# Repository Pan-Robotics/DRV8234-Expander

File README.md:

# DRV8234-Expander
Breakout PCB for The DRV8234 DC Motor Driver

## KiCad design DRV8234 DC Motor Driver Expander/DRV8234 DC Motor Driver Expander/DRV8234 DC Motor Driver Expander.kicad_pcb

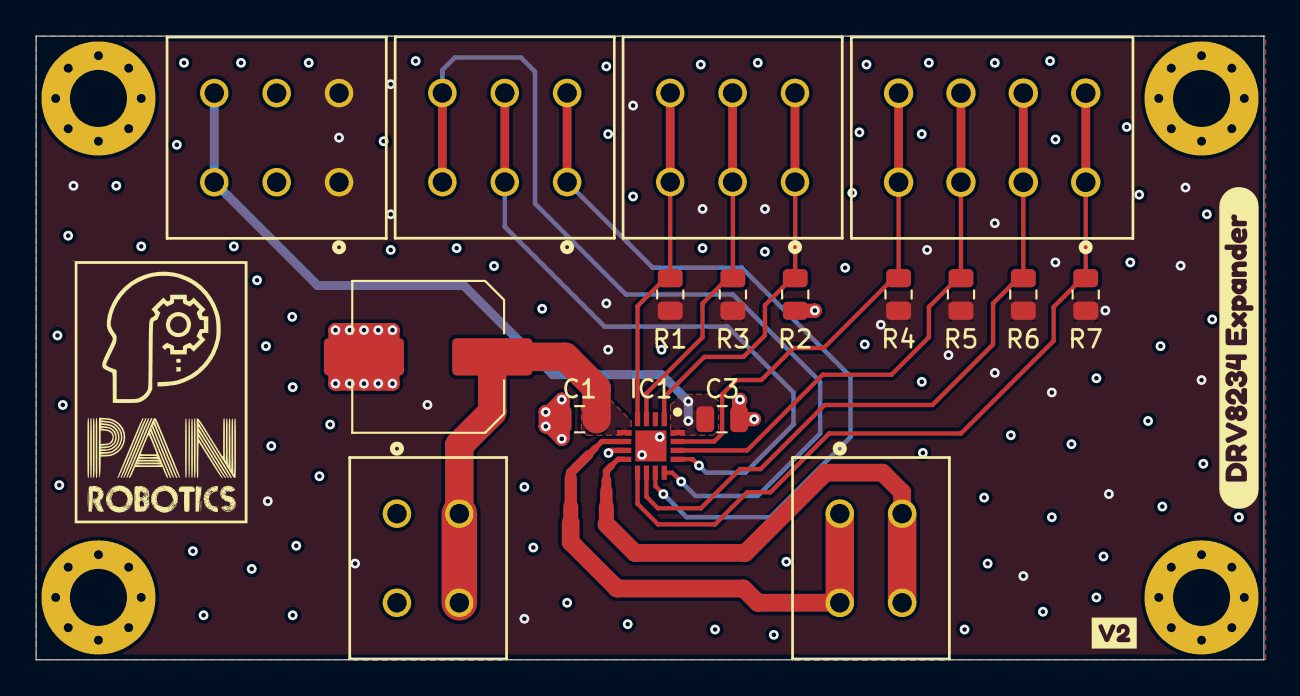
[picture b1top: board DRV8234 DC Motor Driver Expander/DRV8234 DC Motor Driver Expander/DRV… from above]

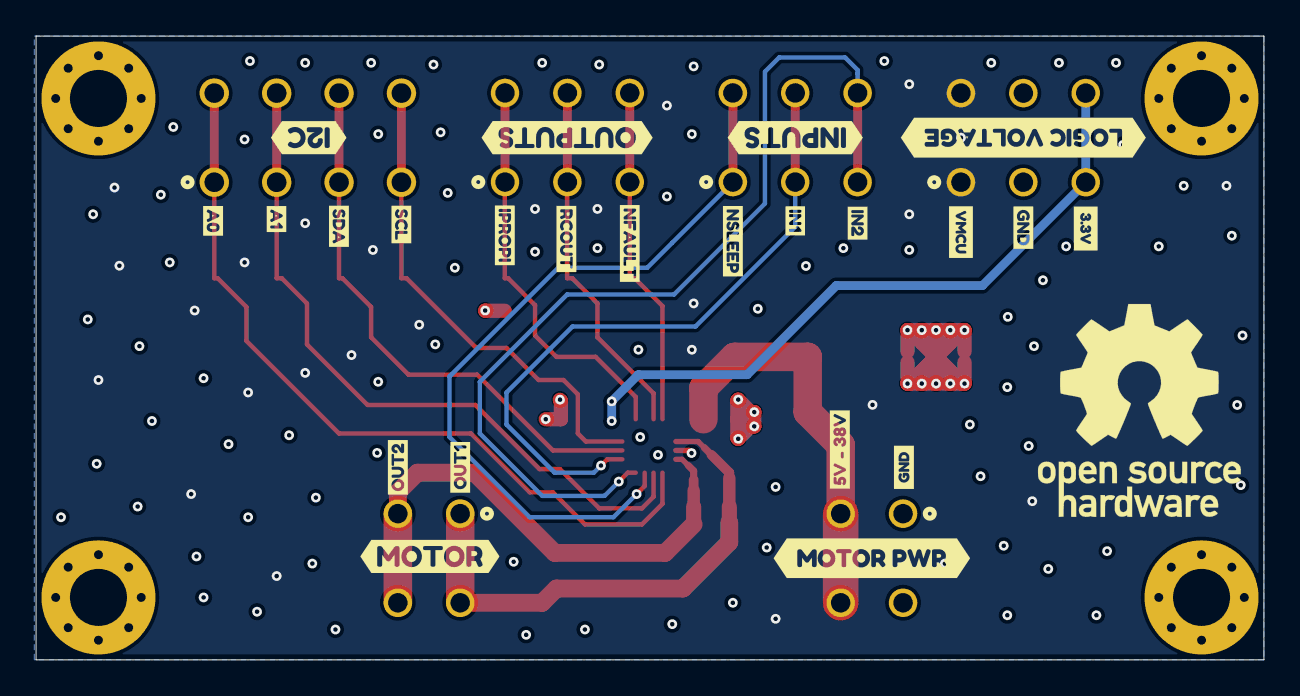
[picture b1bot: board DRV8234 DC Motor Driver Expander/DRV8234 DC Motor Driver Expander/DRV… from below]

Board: 4 copper layers, 68.9 x 35.0 mm, 46 parts (23 on the bottom side), 16 nets.

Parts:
C1, C3: 100nF; C_0805_2012Metric
C2: 100uF; C_Elec_8x10.2
H1, H2, H3, H4: MountingHole; MountingHole_3.2mm_M3_Pad_Via
IC1: DRV8234RTER
J1, J5: CONN_1862042; 1862042
J2, J3, J6: CONN_1862055; 1862055
J4: 1862068
R1, R3: 10k; R_0805_2012Metric
R2: 1.2k; R_0805_2012Metric
R4, R5, R6, R7: 2.2k; R_0805_2012Metric
kibuzzard-65A6FC0C: G***; kibuzzard-65A6FC0C
kibuzzard-65A6FC26: G***; kibuzzard-65A6FC26
kibuzzard-65A6FCAC: G***; kibuzzard-65A6FCAC
kibuzzard-65A6FCCE: G***; kibuzzard-65A6FCCE
kibuzzard-65A6FCD9: G***; kibuzzard-65A6FCD9
kibuzzard-65A6FCE2: G***; kibuzzard-65A6FCE2
kibuzzard-65A6FCF1: G***; kibuzzard-65A6FCF1
kibuzzard-65A6FD0F: G***; kibuzzard-65A6FD0F
kibuzzard-65A6FD3E: G***; kibuzzard-65A6FD3E
kibuzzard-65A6FD04: G***; kibuzzard-65A6FD04
kibuzzard-65A6FD18: G***; kibuzzard-65A6FD18
kibuzzard-65A6FD21: G***; kibuzzard-65A6FD21
kibuzzard-65A6FD28: G***; kibuzzard-65A6FD28
kibuzzard-65A6FD36: G***; kibuzzard-65A6FD36
kibuzzard-65A6FFBA: G***; kibuzzard-65A6FFBA
kibuzzard-65A6FFF9: G***; kibuzzard-65A6FFF9
kibuzzard-65A7001B: G***; kibuzzard-65A7001B
kibuzzard-65A70003: G***; kibuzzard-65A70003
kibuzzard-66A11A0B: G***; kibuzzard-66A11A0B
kibuzzard-66A11A2A: G***; kibuzzard-66A11A2A
kibuzzard-66A11B65: G***; kibuzzard-66A11B65
kibuzzard-66A118A5: G***; kibuzzard-66A118A5
kibuzzard-66A118C9: G***; kibuzzard-66A118C9
kibuzzard-66A1197F: G***; kibuzzard-66A1197F
kibuzzard-66A13964: G***; kibuzzard-66A13964

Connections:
+3V3: C3.1, IC1.16 (VREF), J6.5, J6.6
A0: IC1.10 (A0), J4.3, J4.4, R6.2
A1: IC1.9 (A1), J4.1, J4.2, R7.2
GND: C1.2, C2.2, C3.2, IC1.7 (GND), IC1.17 (EP), J1.1, J1.2, J6.3, J6.4, R2.2
IN1: IC1.13 (EN/IN1), J2.3, J2.4
IN2: IC1.12 (PH/IN2), J2.5, J2.6
IPROPI: IC1.1 (IPROPI), J3.1, J3.2, R2.1
NFAULT: IC1.4 (NFAULT), J3.5, J3.6, R1.2
NSLEEP: IC1.11 (NSLEEP), J2.1, J2.2
OUT1: IC1.6 (OUT1), J5.1, J5.2
OUT2: IC1.8 (OUT2), J5.3, J5.4
RC_OUT: IC1.3 (RC_OUT), J3.3, J3.4, R3.2
SCL: IC1.15 (SCL), J4.7, J4.8, R4.2
SDA: IC1.14 (SDA), J4.5, J4.6, R5.2
VCC_MCU: J6.1, J6.2, R1.1, R3.1, R4.1, R5.1, R6.1, R7.1
VM: C1.1, C2.1, IC1.5 (VM), J1.3, J1.4

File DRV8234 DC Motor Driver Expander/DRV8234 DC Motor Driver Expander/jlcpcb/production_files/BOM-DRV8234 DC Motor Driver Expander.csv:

Comment,Designator,Footprint,LCSC
10K,R1,R_0805_2012Metric_Pad1.20x1.40mm_HandSolder,
CNTRL_OUT,J3,CONN_1862055,
MOTOR,J5,CONN_1862042,
2.2K,R6,R_0805_2012Metric_Pad1.20x1.40mm_HandSolder,
100uF,C2,C_Elec_8x10.2,
8.45K,R2,R_0805_2012Metric_Pad1.20x1.40mm_HandSolder,
CNTRL_IN,J2,CONN_1862055,
POWER,J1,CONN_1862055,
MountingHole,H2,MountingHole_3.2mm_M3_Pad_Via,
DRV8234RTER,IC1,QFN50P300X300X80-17N-D,
MountingHole,H3,MountingHole_3.2mm_M3_Pad_Via,
2.2K,R4,R_0805_2012Metric_Pad1.20x1.40mm_HandSolder,
2.2K,R5,R_0805_2012Metric_Pad1.20x1.40mm_HandSolder,
2.2K,R7,R_0805_2012Metric_Pad1.20x1.40mm_HandSolder,
10K,R3,R_0805_2012Metric_Pad1.20x1.40mm_HandSolder,
100nF,C3,C_1206_3216Metric_Pad1.33x1.80mm_HandSolder,
100nF,C1,C_1206_3216Metric_Pad1.33x1.80mm_HandSolder,
I2C,J4,1862068,
MountingHole,H1,MountingHole_3.2mm_M3_Pad_Via,
MountingHole,H4,MountingHole_3.2mm_M3_Pad_Via,

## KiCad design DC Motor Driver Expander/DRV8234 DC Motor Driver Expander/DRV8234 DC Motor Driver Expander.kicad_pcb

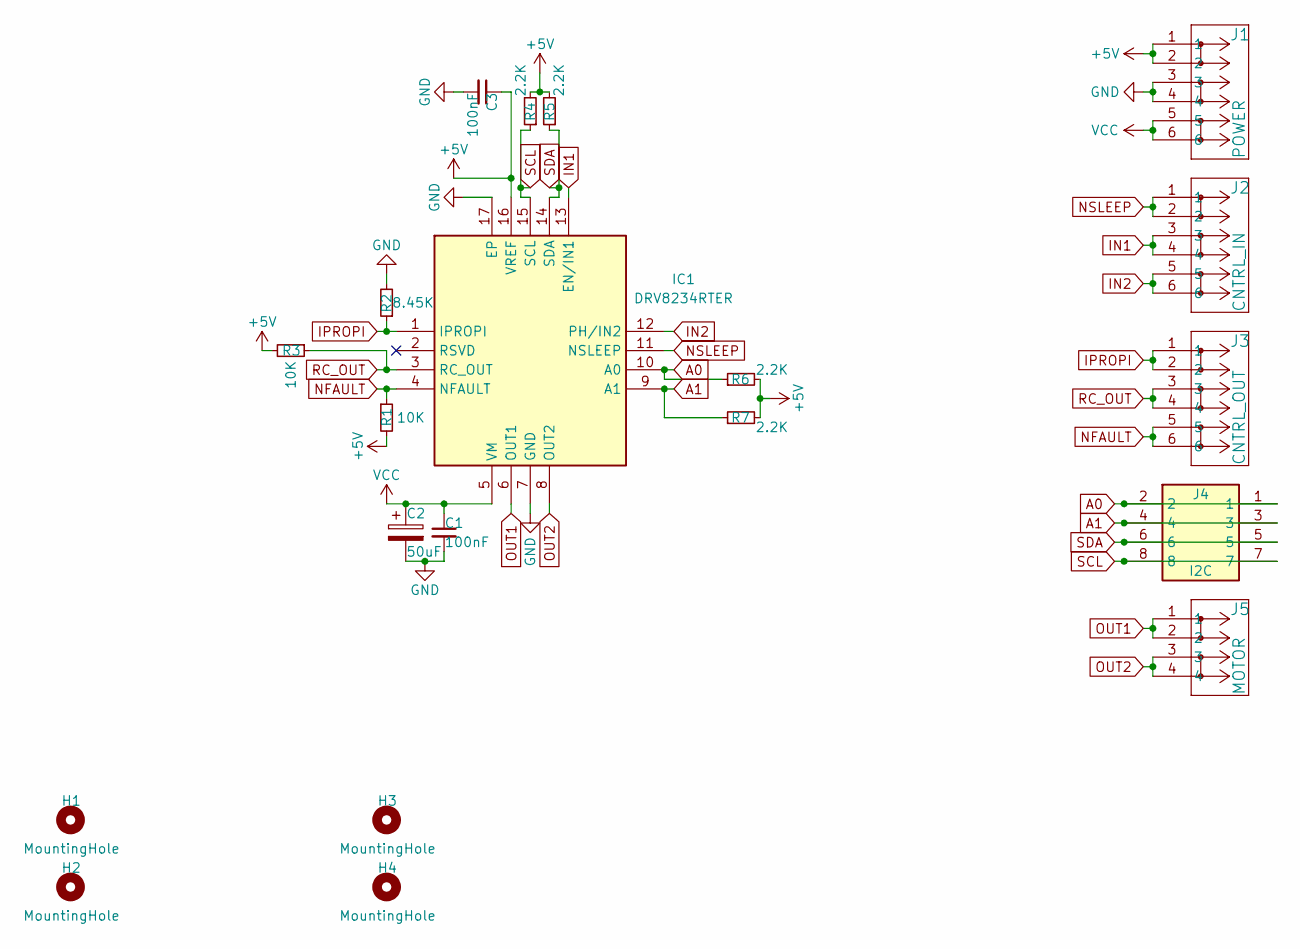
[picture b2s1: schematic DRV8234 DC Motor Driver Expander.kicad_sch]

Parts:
C1, C3: 100nF; C_1206_3216Metric_Pad1.33x1.80mm_HandSolder
C2: 50uF; C_Elec_5x5.8
H1, H2, H3, H4: MountingHole; MountingHole_3.2mm_M3_Pad_Via
IC1: DRV8234RTER; QFN50P300X300X80-17N-D; Manufacturer_Part_Number DRV8234RTER
J1: POWER; CONN_1862055
J2: CNTRL_IN; CONN_1862055
J3: CNTRL_OUT; CONN_1862055
J4: I2C; 1862068; Mouser Part Number 651-1862068
J5: MOTOR; CONN_1862042
R1, R3: 10K; R_0805_2012Metric_Pad1.20x1.40mm_HandSolder
R2: 8.45K; R_0805_2012Metric_Pad1.20x1.40mm_HandSolder
R4, R5, R6, R7: 2.2K; R_0805_2012Metric_Pad1.20x1.40mm_HandSolder

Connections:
+5V: C3.1, IC1.16 (VREF), J1.1, J1.2, R1.2, R3.2, R4.2, R5.2, R6.2, R7.2
A0: IC1.10 (A0), J4.1, J4.2, R6.1
A1: IC1.9 (A1), J4.3, J4.4, R7.1
GND: C1.2, C2.2, C3.2, IC1.7 (GND), IC1.17 (EP), J1.3, J1.4, R2.2
IN1: IC1.13 (EN/IN1), J2.3, J2.4
IN2: IC1.12 (PH/IN2), J2.5, J2.6
IPROPI: IC1.1 (IPROPI), J3.1, J3.2, R2.1
NFAULT: IC1.4 (NFAULT), J3.5, J3.6, R1.1
NSLEEP: IC1.11 (NSLEEP), J2.1, J2.2
OUT1: IC1.6 (OUT1), J5.1, J5.2
OUT2: IC1.8 (OUT2), J5.3, J5.4
RC_OUT: IC1.3 (RC_OUT), J3.3, J3.4, R3.1
SCL: IC1.15 (SCL), J4.7, J4.8, R4.1
SDA: IC1.14 (SDA), J4.5, J4.6, R5.1
VCC: C1.1, C2.1, IC1.5 (VM), J1.5, J1.6

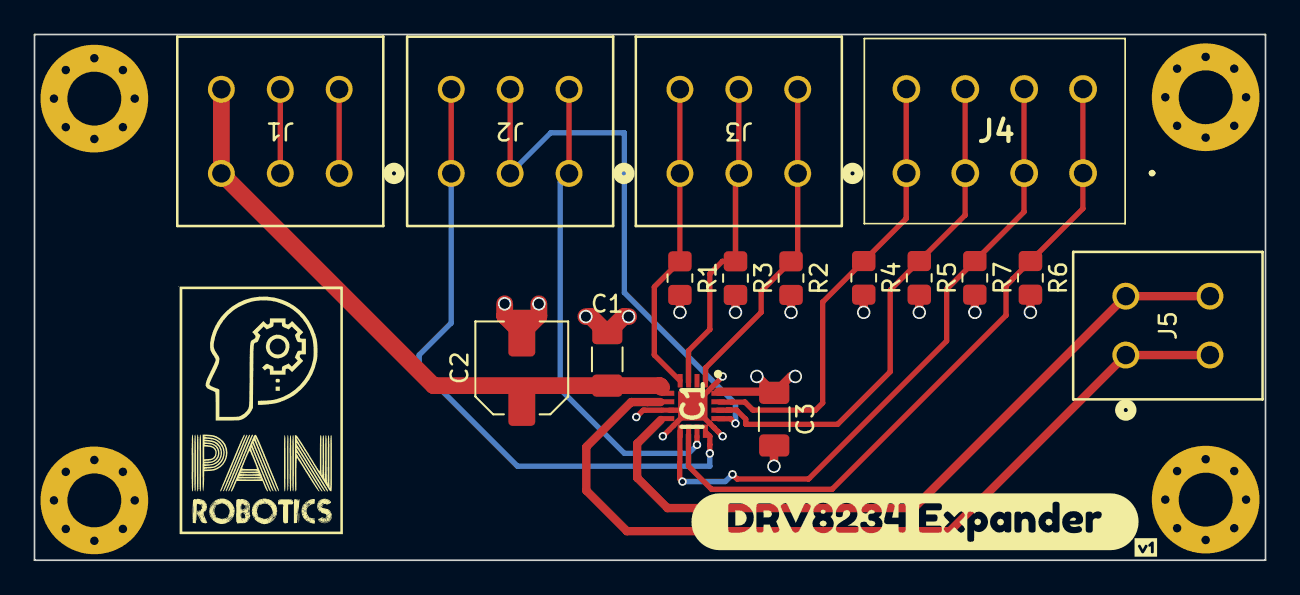
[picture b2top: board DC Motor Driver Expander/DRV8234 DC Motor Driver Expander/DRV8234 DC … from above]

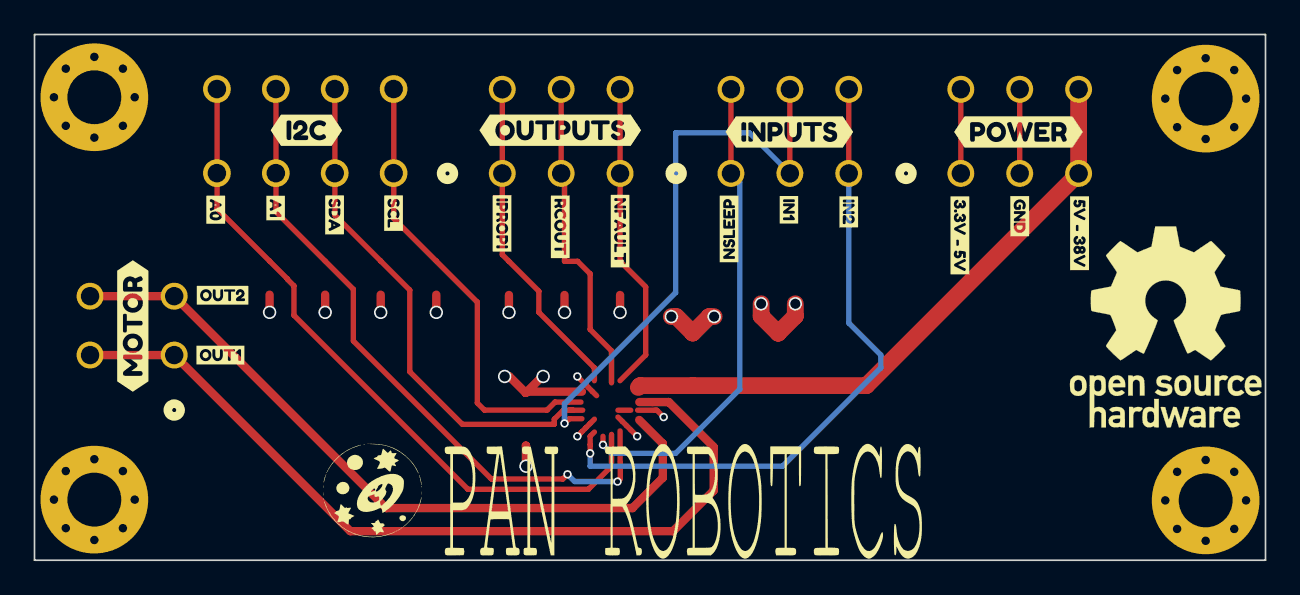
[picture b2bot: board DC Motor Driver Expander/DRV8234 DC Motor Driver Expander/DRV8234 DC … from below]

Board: 4 copper layers, 73.2 x 31.2 mm, 42 parts (20 on the bottom side), 15 nets.

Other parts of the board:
kibuzzard-65A6FC0C: G***; kibuzzard-65A6FC0C
kibuzzard-65A6FC4F: G***; kibuzzard-65A6FC4F
kibuzzard-65A6FC26: G***; kibuzzard-65A6FC26
kibuzzard-65A6FCAC: G***; kibuzzard-65A6FCAC
kibuzzard-65A6FCCE: G***; kibuzzard-65A6FCCE
kibuzzard-65A6FCD9: G***; kibuzzard-65A6FCD9
kibuzzard-65A6FCE2: G***; kibuzzard-65A6FCE2
kibuzzard-65A6FCF1: G***; kibuzzard-65A6FCF1
kibuzzard-65A6FD0F: G***; kibuzzard-65A6FD0F
kibuzzard-65A6FD3E: G***; kibuzzard-65A6FD3E
kibuzzard-65A6FD04: G***; kibuzzard-65A6FD04
kibuzzard-65A6FD18: G***; kibuzzard-65A6FD18
kibuzzard-65A6FD21: G***; kibuzzard-65A6FD21
kibuzzard-65A6FD28: G***; kibuzzard-65A6FD28
kibuzzard-65A6FD36: G***; kibuzzard-65A6FD36
kibuzzard-65A6FFBA: G***; kibuzzard-65A6FFBA
kibuzzard-65A6FFF9: G***; kibuzzard-65A6FFF9
kibuzzard-65A7000E: G***; kibuzzard-65A7000E
kibuzzard-65A7001B: G***; kibuzzard-65A7001B
kibuzzard-65A7036D: G***; kibuzzard-65A7036D
kibuzzard-65A7039D: G***; kibuzzard-65A7039D
kibuzzard-65A70003: G***; kibuzzard-65A70003

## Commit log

2024-01-17 Initial Commit
    Breakout for DRV8234 2-A Brushed DC Motor Driver with Ripple Counting, Stall Detection, and
    Speed Regulation
    Push Terminal Breakout PCB
2024-01-19 Update
    BOM Added
    50uF -> 100uF Capacitor
2024-07-24 docs update
